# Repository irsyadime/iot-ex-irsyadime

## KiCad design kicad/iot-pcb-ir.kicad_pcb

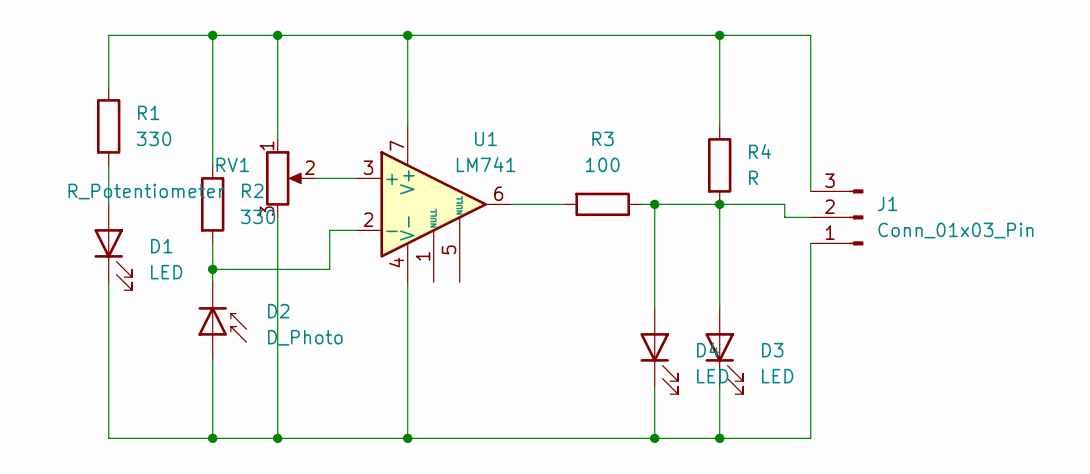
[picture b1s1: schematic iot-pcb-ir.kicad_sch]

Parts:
D1: LED; LED_D4.0mm
D2: D_Photo; LED_D4.0mm
D3, D4: LED; LED_0805_2012Metric_Pad1.15x1.40mm_HandSolder
J1: Conn_01x03_Pin; PinHeader_1x03_P2.54mm_Horizontal
R1, R2: 330; R_0805_2012Metric
R3: 100; R_0805_2012Metric
R4: R; R_0805_2012Metric
RV1: R_Potentiometer; Potentiometer_ACP_CA9-V10_Vertical_Hole
U1: LM741; SOIC-8_3.9x4.9mm_P1.27mm

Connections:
unnamed: D1.2 (A), R1.2
unnamed: D1.1 (K), D2.2 (A), D3.1 (K), D4.1 (K), J1.1, RV1.3, U1.4 (V-)
unnamed: D2.1 (K), R2.2, U1.2 (-)
unnamed: D3.2 (A), D4.2 (A), J1.2, R3.1, R4.2
unnamed: J1.3, R1.1, R2.1, R4.1, RV1.1, U1.7 (V+)
unnamed: R3.2, U1.6
unnamed: RV1.2, U1.3 (+)

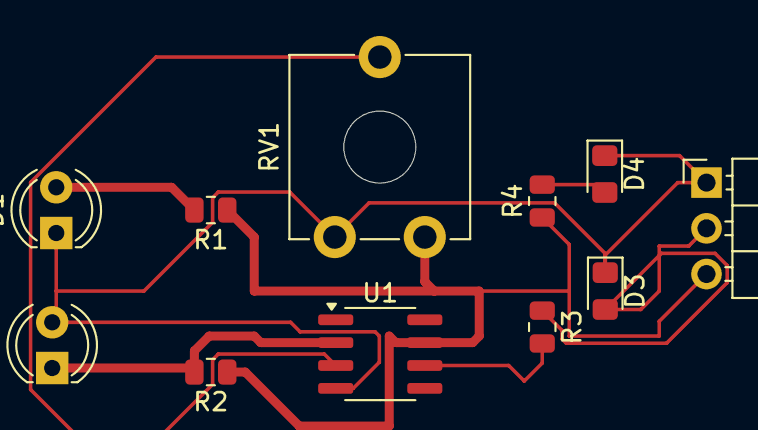
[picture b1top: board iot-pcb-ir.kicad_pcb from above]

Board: 2 copper layers, 11 parts (0 on the bottom side), 7 nets.

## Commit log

2024-04-27 initial commit, task done
